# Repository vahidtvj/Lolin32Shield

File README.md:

# Lolin 32 Shield

A collection of useful stuff to have on a ESP32 dev board

## Whats on the board?

- A Micro SD card
- **DS1307**, `for time keeping`
- Battery Switch
- Battery Probe `(This is Builtin on Lolin d32 board)`
- Passive Buzzer, `when you want to annoy others!`
- QC3 capable USB port, `so you can have 12v`
- PWM controlled header, `in case you want to control sth high power (usable with QC)`
- A voltage booster, `cuz some modules just don't work with 3.3v`
- And Mosfets, `To shut everthing off`

## GPIO Wiring

|                         PIN                         | GPIO |
| :-------------------------------------------------: | :--: |
|                        SD_CS                        |  5   |
| <span style="text-decoration:overline">SD_EN</span> |  33  |
|                       BUZZER                        |  32  |
|                        VBAT                         |  35  |
|                      BOOST_EN                       |  27  |
|                       USB_DM                        |  17  |
|                       USB_DP                        |  16  |
|                       MOSFET                        |  4   |

### Some Notes

Due to availability, I had to use _DS1307_ RTC chip. **PCF8523T** is a much better alternative. DS1307 requires 5v to operate, so when powering from a lipo battery you have to enable the voltage booster.

SD card can be disabled using **SD_EN** PIN to save power. Don't forget to set it low before trying to read the card.

The USB_C port is there so you can connect a second power source (**Not connected to ESP**). This is useful when you have devices that draw more current and your laptop's usb ports can't supply enough power.
Also Quick Charge Enabled Adapters can be used to get higher voltages like 12v ( `voltage level is controlled by the ESP, checkout `[QC3Control](https://github.com/vahidtvj/QC3Control) ).

### Future Changes

- **PCF8523T** as a drop-in replacement for _DS1307_
- 3.3v Regulator for USB_C input (has to work with QC3 voltage levels)
- A RESET Button

## License

This project is licensed under the [MIT License](LICENSE)

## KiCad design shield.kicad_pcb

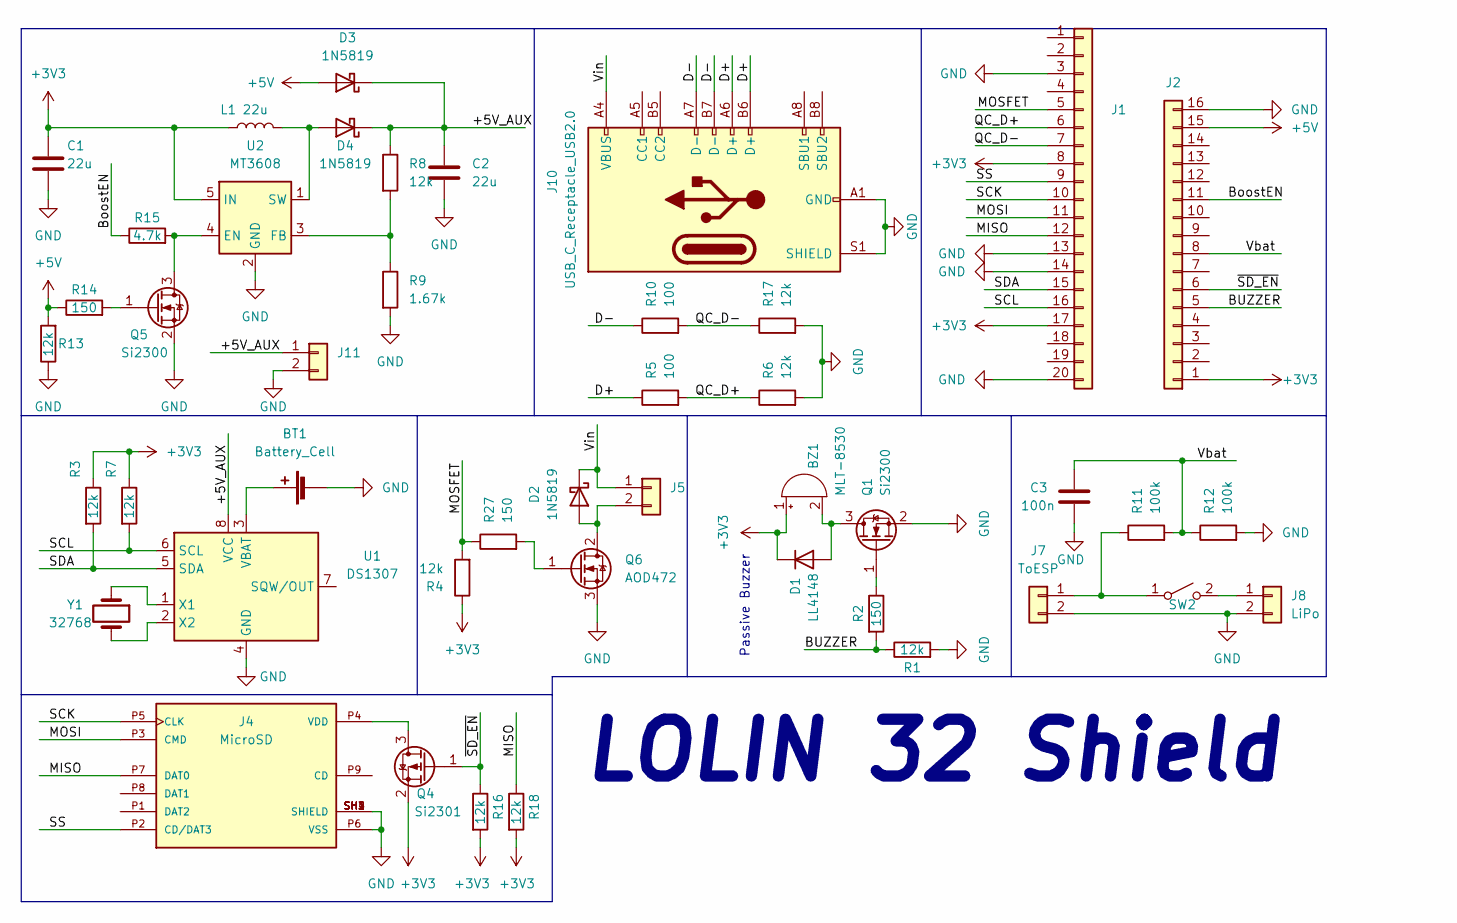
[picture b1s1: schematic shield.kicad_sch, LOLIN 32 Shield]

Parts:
BT1: Battery_Cell; CR1220Holder_SMD
BZ1: MLT-8530; MagneticBuzzer_Kobitone_254-EMB84Q-RO
C1, C2: 22u; C_0805_2012Metric_Pad1.18x1.45mm_HandSolder
C3: 100n; C_0805_2012Metric_Pad1.18x1.45mm_HandSolder
D1: LL4148; D_MiniMELF
D2: 1N5819; D_SMA
D3, D4: 1N5819; Nexperia_CFP3_SOD-123W
J1: Conn_01x20; PinSocket_1x20_P2.54mm_Vertical
J2: Conn_01x16; PinSocket_1x16_P2.54mm_Vertical
J4: MicroSD; GCT_MEM2075-00-140-01-A; PARTREV A
J5: Conn_01x02; JST_XH_B2B-XH-A_1x02_P2.50mm_Vertical
J7: ToESP; PinHeader_1x02_P2.00mm_Vertical
J8: LiPo; JST_XH_S2B-XH-A_1x02_P2.50mm_Horizontal
J10: USB_C_Receptacle_USB2.0; USB_C_Receptacle_HRO_TYPE-C-31-M-12
J11: Conn_01x02; PinHeader_1x02_P2.54mm_Vertical
L1: 22u; L_Bourns-SRN8040_8x8.15mm
Q1, Q5: Si2300; SOT-23
Q4: Si2301; SOT-23
Q6: AOD472; TO-252-2
R1, R3, R4, R6, R7, R8, R13, R16, R17, R18: 12k; R_0603_1608Metric_Pad0.98x0.95mm_HandSolder
R2, R14, R27: 150; R_0603_1608Metric_Pad0.98x0.95mm_HandSolder
R5, R10: 100; R_0603_1608Metric_Pad0.98x0.95mm_HandSolder
R9: 1.67k; R_0603_1608Metric_Pad0.98x0.95mm_HandSolder
R11, R12: 100k; R_0805_2012Metric_Pad1.20x1.40mm_HandSolder
R15: 4.7k; R_0603_1608Metric_Pad0.98x0.95mm_HandSolder
SW2: SW_SPST; SW_Slide_1P2T_CK_OS102011MS2Q
U1: DS1307; SOIC-8_3.9x4.9mm_P1.27mm
U2: MT3608; SOT-23-6
Y1: 32768; Crystal_DS26_D2.0mm_L6.0mm_Horizontal_1EP_style1

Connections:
+3V3: BZ1.1 (-), C1.1, D1.1 (K), J1.8, J1.17, J2.1, L1.1, Q4.2 (S), R3.1, R4.1, R7.1, R16.2, R18.2, U2.5 (IN)
+5V: D3.2 (A), J2.15, R13.2, R14.1
/+5V_AUX: C2.1, D3.1 (K), D4.1 (K), J11.1, R8.1, U1.8 (VCC)
/BUZZER: J2.5, R1.1, R2.2
/BoostEN: J2.11, R15.1
/D+: J10.A6 (D+), J10.B6 (D+), R5.1
/D-: J10.A7 (D-), J10.B7 (D-), R10.1
/MISO: J1.12, J4.P7 (DAT0), R18.1
/MOSFET: J1.5, R4.2, R27.1
/MOSI: J1.11, J4.P3 (CMD)
/QC_D+: J1.6, R5.2, R6.1
/QC_D-: J1.7, R10.2, R17.1
/SCK: J1.10, J4.P5 (CLK)
/SCL: J1.16, R7.2, U1.6 (SCL)
/SDA: J1.15, R3.2, U1.5 (SDA)
/SD_EN: J2.6, Q4.1 (G), R16.1
/SS: J1.9, J4.P2 (CD/DAT3)
/Vbat: C3.2, J2.8, R11.2, R12.1
/Vin: D2.1 (K), J5.1, J10.A4 (VBUS), J10.A9 (VBUS), J10.B4 (VBUS), J10.B9 (VBUS); also elsewhere on the board
GND: BT1.2 (-), C1.2, C2.2, C3.1, J1.3, J1.13, J1.14, J1.20, J2.16, J4.P6 (VSS), J4.SH1 (SHIELD), J4.SH2 (SHIELD), J4.SH3 (SHIELD), J4.SH4 (SHIELD), J7.2, J8.2, J10.A1 (GND), J10.A12 (GND), J10.B1 (GND), J10.B12 (GND), J10.S1 (SHIELD), J11.2, Q1.2 (S), Q5.2 (S), Q6.3 (S), R1.2, R6.2, R9.2, R12.2, R13.1, R17.2, U1.4 (GND), U2.2 (GND); also elsewhere on the board
unnamed: BT1.1 (+), U1.3 (VBAT)
unnamed: BZ1.2 (+), D1.2 (A), Q1.3 (D)
unnamed: D2.2 (A), J5.2, Q6.2 (D)
unnamed: D4.2 (A), L1.2, U2.1 (SW)
unnamed: J4.P4 (VDD), Q4.3 (D)
unnamed: J7.1, R11.1, SW2.1 (A)
unnamed: J8.1, SW2.2 (B)
unnamed: Q1.1 (G), R2.1
unnamed: Q5.1 (G), R14.2
unnamed: Q5.3 (D), R15.2, U2.4 (EN)
unnamed: Q6.1 (G), R27.2
unnamed: R8.2, R9.1, U2.3 (FB)
unnamed: U1.1 (X1), Y1.1
unnamed: U1.2 (X2), Y1.2

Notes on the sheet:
Passive Buzzer
LOLIN 32 Shield

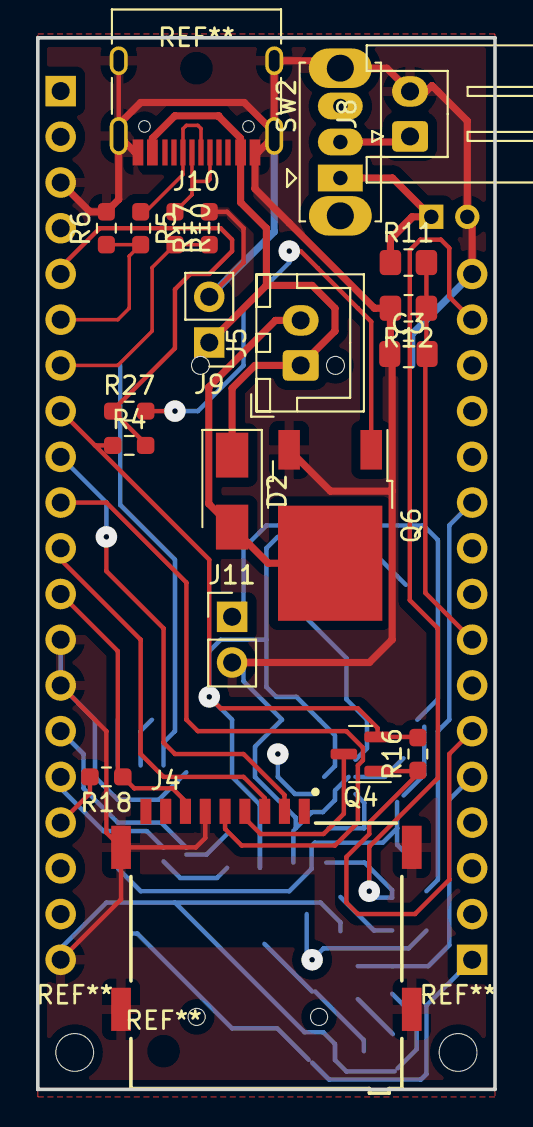
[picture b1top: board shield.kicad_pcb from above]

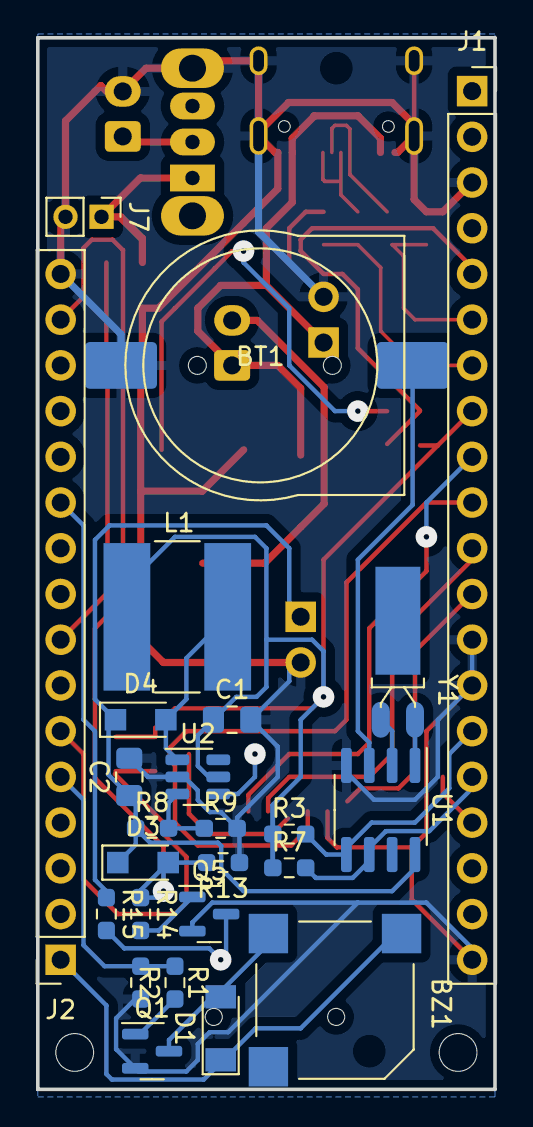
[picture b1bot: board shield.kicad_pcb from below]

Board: 4 copper layers, 25.4 x 58.4 mm, 46 parts (25 on the bottom side), 34 nets.

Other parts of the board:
J9: Conn_01x02; PinHeader_1x02_P2.54mm_Vertical

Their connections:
/Vin: J9.1; also elsewhere on the board
GND: J9.2; also elsewhere on the board
